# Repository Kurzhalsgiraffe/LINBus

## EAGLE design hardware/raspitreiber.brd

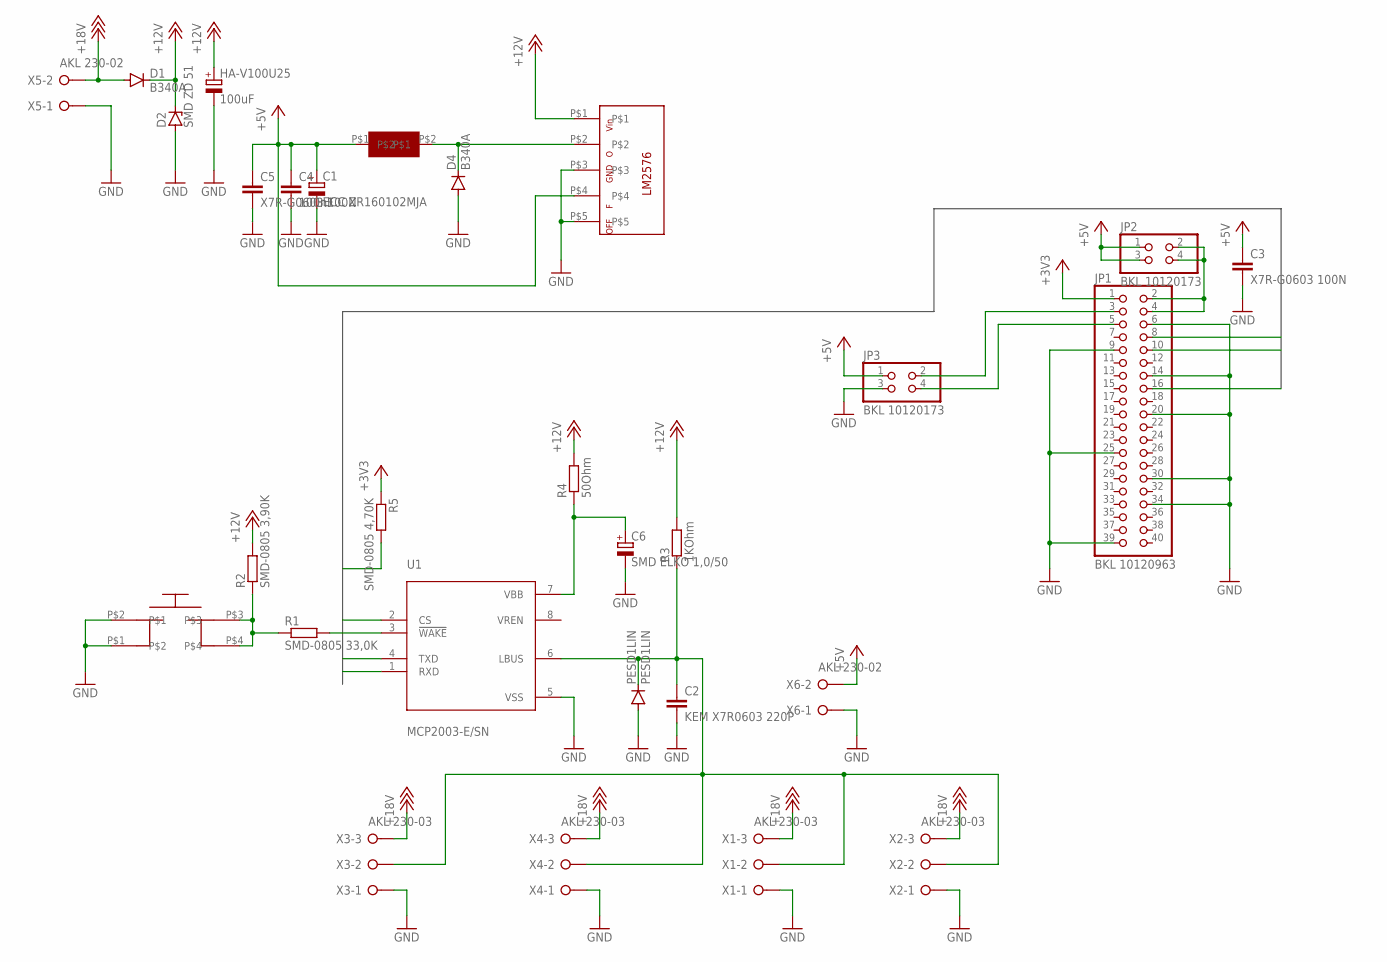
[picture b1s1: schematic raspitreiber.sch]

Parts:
C1: ECC ZR160102MJA; 153CLV-1012
C2: KEM X7R0603 220P; C0603
C3, C5: X7R-G0603 100N; C0603
C4: 100nF; C0603
C6: SMD ELKO 1,0/50; 150CLZ-0810
D1, D4: B340A; SMC
D2: SMD ZD 51; SOT23
HA-V100U25: 100uF; 153CLV-0807
JP1: BKL 10120963; 2X20
JP2, JP3: BKL 10120173; 2X02
L-09HVP100: LDEVICE7MM; LFOOT7MM
PESD1LIN: PESD1LIN; SOD323-W
R1: SMD-0805 33,0K; M0805
R2: SMD-0805 3,90K; M0805
R3: 1KOhm; M0805
R4: 50Ohm; M0805
R5: SMD-0805 4,70K; M0805
TASTER9313: SCHALTDEV; SCHALTFOOT
U1: MCP2003-E/SN; SOIC127P600X175-8N
U$1: LM2576
X1, X2, X3, X4: AKL 230-03; W237-3E
X5, X6: AKL 230-02; W237-132

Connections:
+3V3: JP1.1, R5.1
+5V: C1.+, C3.1, C4.1, C5.1, JP2.1, JP2.3, JP3.1, L-09HVP100.P$1, U$1.P$4, X6.2
+12V: D1.C, D2.3 (C), HA-V100U25.+, R2.2, R3.2, R4.2, U$1.P$1
+18V: D1.A, X1.3, X2.3, X3.3, X4.3, X5.2
CS: JP1.16, U1.2 (CS)
GND: C1.-, C2.2, C3.2, C4.2, C5.2, C6.-, D2.1 (A), D4.A, HA-V100U25.-, JP1.6, JP1.9, JP1.14, JP1.20, JP1.25, JP1.30, JP1.34, JP1.39, JP3.3, PESD1LIN.A, TASTER9313.P$1, TASTER9313.P$2, U1.5 (VSS), U$1.P$3, U$1.P$5, X1.1, X2.1, X3.1, X4.1, X5.1, X6.1
unnamed: D4.C, L-09HVP100.P$2, U$1.P$2
unnamed: C6.+, R4.1, U1.7 (VBB)
unnamed: R1.1, R2.1, TASTER9313.P$3, TASTER9313.P$4
unnamed: R1.2, U1.3 (!WAKE)
unnamed: C2.1, PESD1LIN.C, R3.1, U1.6 (LBUS), X1.2, X2.2, X3.2, X4.2
unnamed: JP1.2, JP1.4, JP2.2, JP2.4
unnamed: JP1.3, JP3.2
unnamed: JP1.5, JP3.4
RX: JP1.10, R5.2, U1.1 (RXD)
TX: JP1.8, U1.4 (TXD)

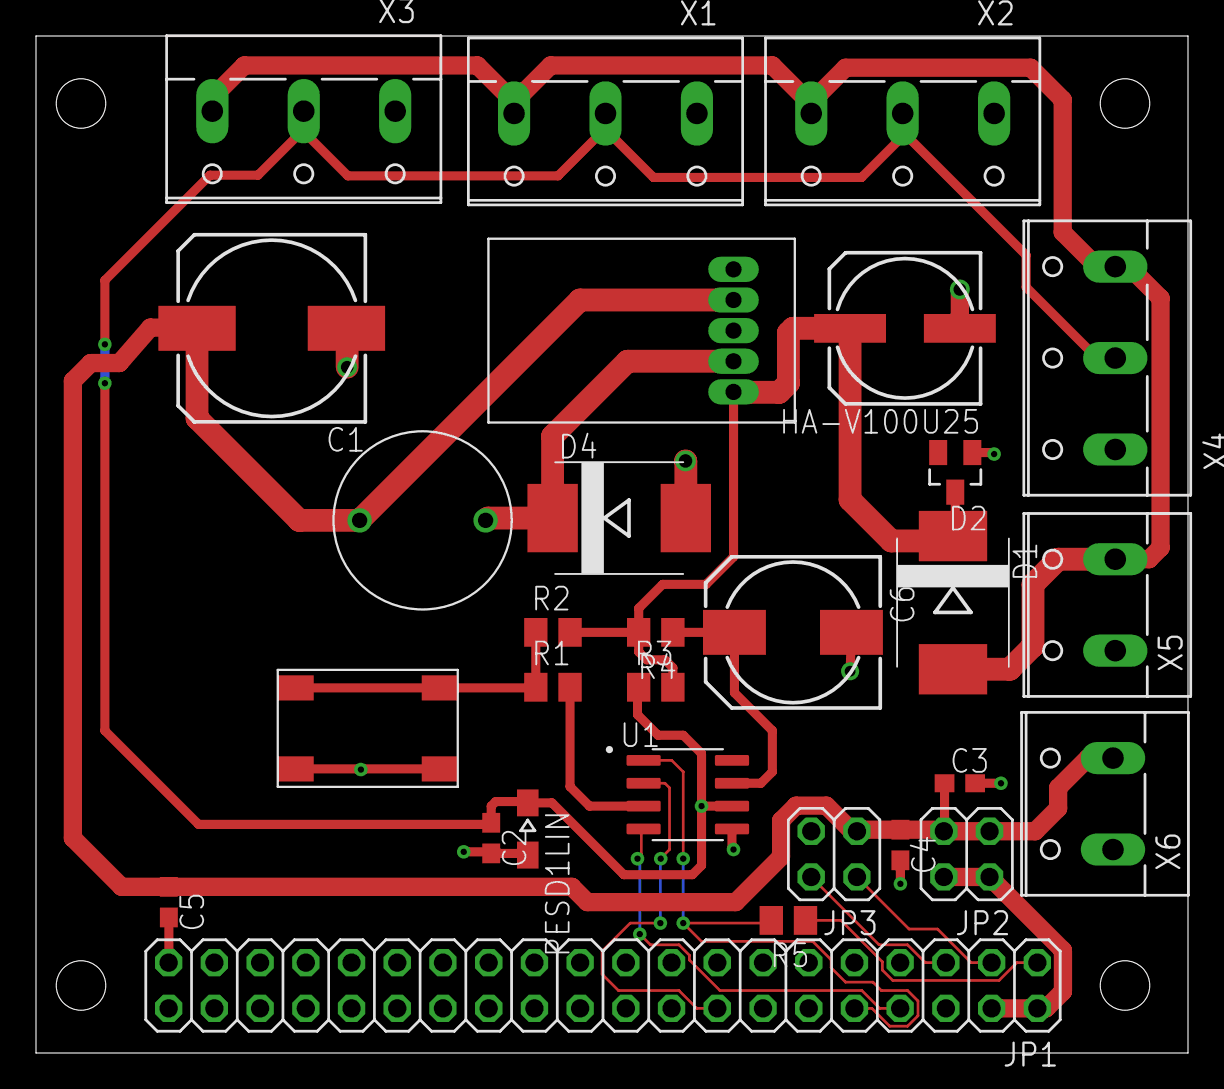
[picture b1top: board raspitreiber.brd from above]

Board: 2 copper layers, 64.0 x 56.5 mm, 29 parts (0 on the bottom side), 16 nets.

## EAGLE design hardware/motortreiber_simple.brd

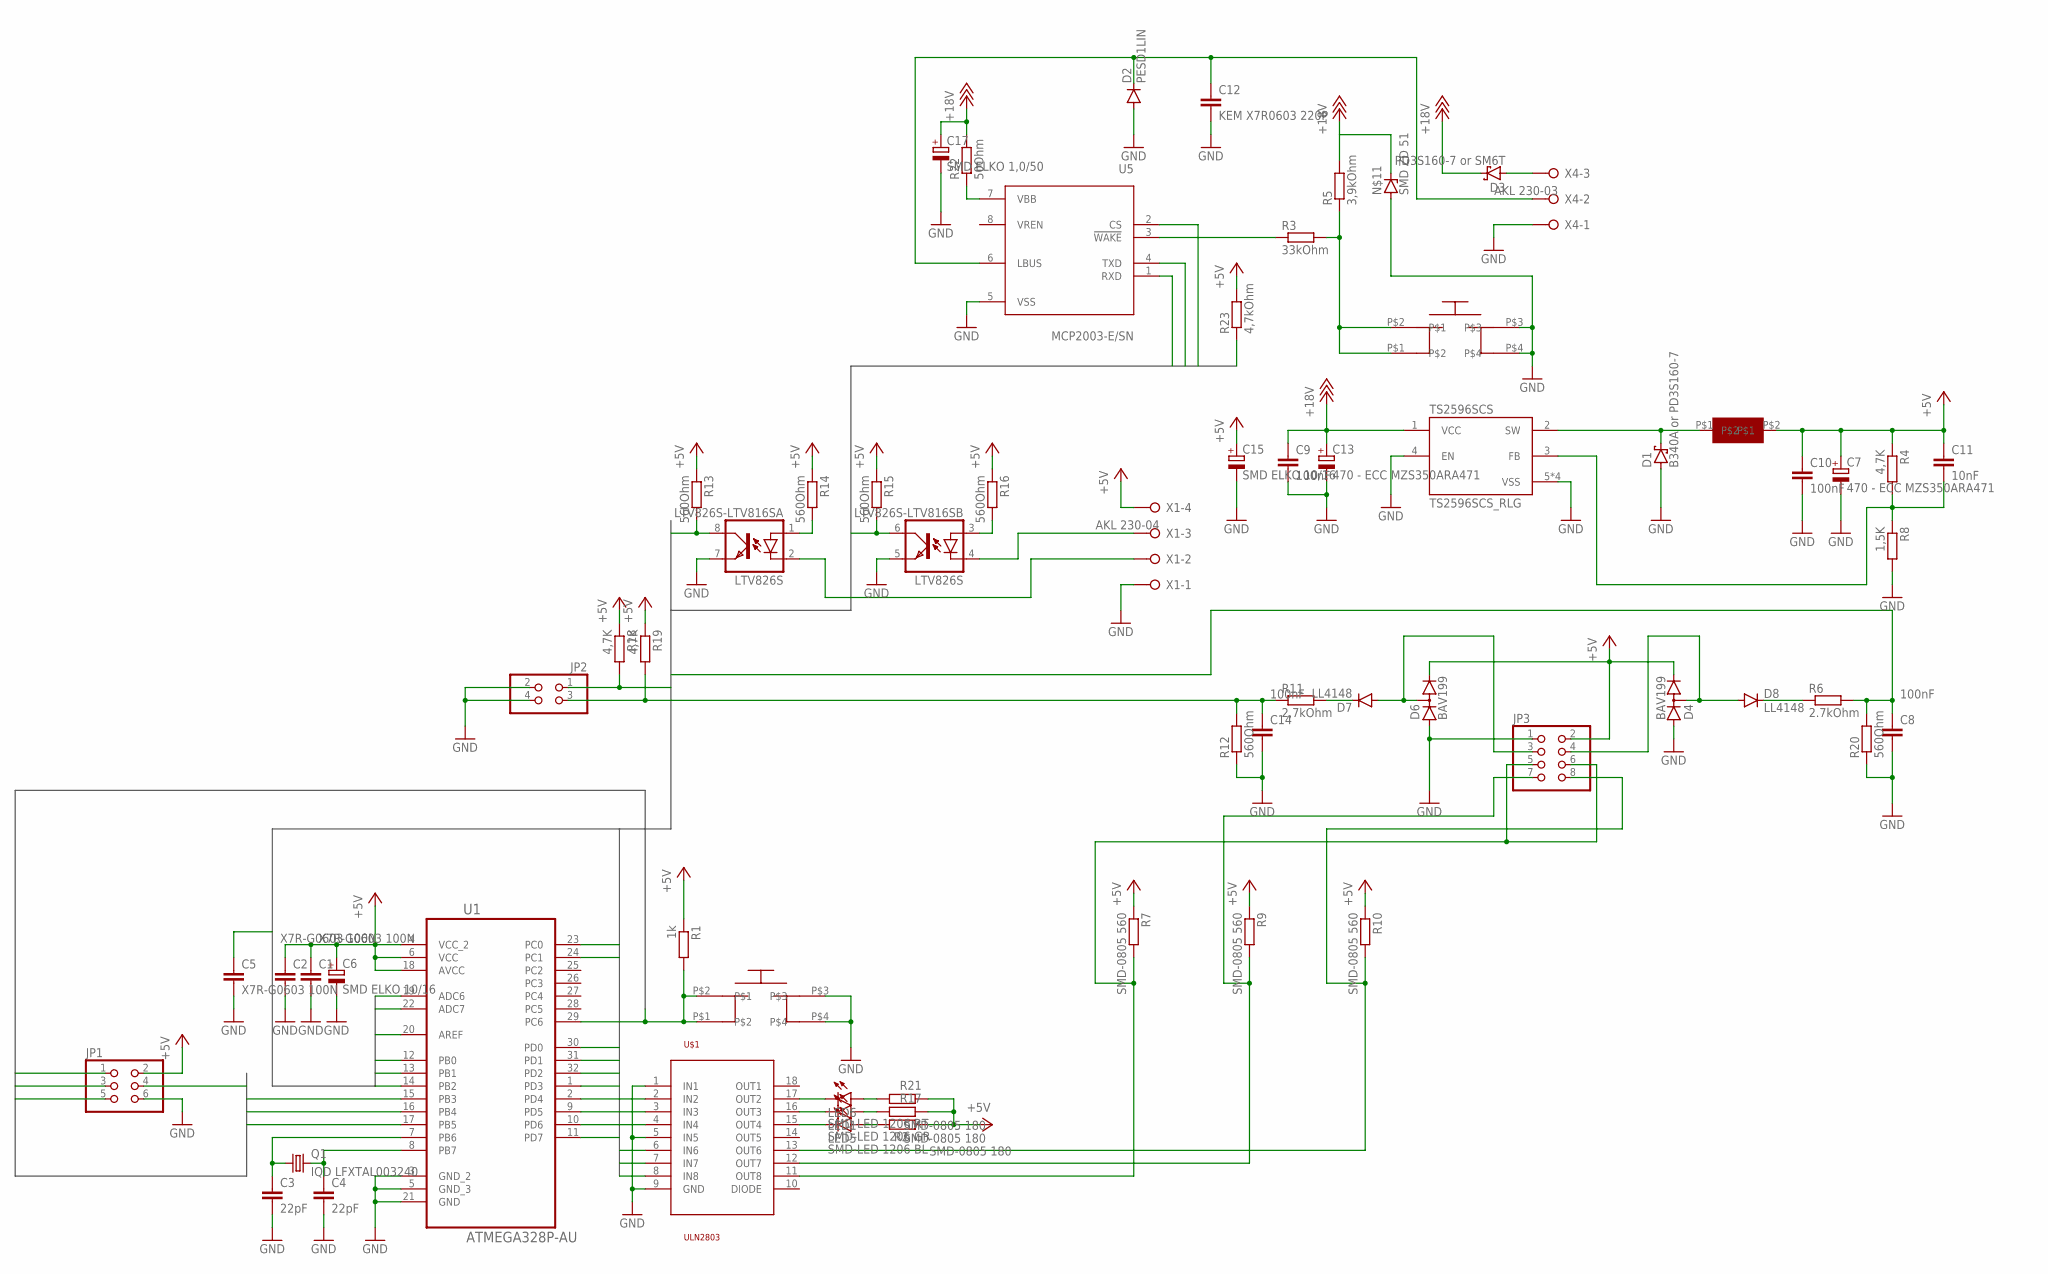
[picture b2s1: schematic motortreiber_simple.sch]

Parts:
C1, C2, C5: X7R-G0603 100N; C0603
C3, C4: 22pF; C0603
C6, C15: SMD ELKO 10/16; 153CLV-0505
C7, C13: 470 - ECC MZS350ARA471; 175TMP-0810
C8, C9, C10, C14: 100nF; C0603
C11: 10nF; C0603
C12: KEM X7R0603 220P; C0603
C17: SMD ELKO 1,0/50; 153CLV-0405
D1: B340A or PD3S160-7; SMB
D2: PESD1LIN; SOD323-W
D3: PD3S160-7 or SM6T; SMB
D4, D6: BAV199; SOT23
D7, D8: LL4148; SOD323-W
JP1: PINHD-2X3; 2X03
JP2: PINHD-2X2; 2X02
JP3: PINHD-2X4; 2X04
L-05HCP33: LDEVICE2-5MM; LFOOT2-5MM
LED1: SMD-LED 1206 GR; CHIPLED_1206
LED5: SMD-LED 1206 BL; CHIPLED_1206
LED6: SMD-LED 1206 RT; CHIPLED_1206
LTV826S-LTV816S: LTV826S; DIL8-SMD
N$11: SMD ZD 51; SOT23
Q1: IQD LFXTAL003240; HC49U-V
R1: 1k; R0805
R2, R17, R21: SMD-0805 180; R0805
R3: 33kOhm; R0805
R4, R18, R19: 4,7K; R0805
R5: 3,9kOhm; R0805
R6: 2.7kOhm; R0805
R7, R9, R10: SMD-0805 560; R0805
R8: 1,5K; R0805
R11: 2,7kOhm; R0805
R12, R13, R14, R15, R16, R20: 560Ohm; R0805
R22: 50Ohm; R0805
R23: 4,7kOhm; R0805
TASTER9313-1, TASTER9313-2: SCHALTDEV; SCHALTFOOT
TS2596SCS: TS2596SCS_RLG; SOP127P600X200-8N
U1: ATMEGA328P-AU; QFP80P900X900X120-32N
U5: MCP2003-E/SN; SOIC127P600X175-8N
U$1: ULN2803; SO18L
X1: AKL 230-04; W237-4P
X4: AKL 230-03; W237-3E

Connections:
+5V: C1.1, C2.1, C6.+, C7.+, C10.1, C11.1, C15.+, D4.2 (C), D6.2 (C), JP1.2, JP3.2, L-05HCP33.P$2, R1.1, R2.1, R4.1, R7.1, R9.1, R10.1, R13.1, R14.1, R15.1, R16.1, R17.1, R18.1, R19.1, R21.1, R23.2, U1.4 (VCC_2), U1.6 (VCC), U1.18 (AVCC), X1.4
+18V: C9.1, C13.+, C17.+, D3.C, N$11.3 (C), R5.2, R22.2, TS2596SCS.1 (VCC)
ADC6: C8.1, R6.2, R20.2, U1.19 (ADC6)
ADC7: C14.1, R11.1, R12.2, U1.22 (ADC7)
AREF: C5.1, U1.20 (AREF)
CLK: JP1.3, U1.17 (PB5)
GND: C1.2, C2.2, C3.2, C4.2, C5.2, C6.-, C7.-, C8.2, C9.2, C10.2, C12.2, C13.-, C14.2, C15.-, C17.-, D1.A, D2.A, D4.1 (A), D6.1 (A), JP1.6, JP2.2, JP2.4, JP3.1, LTV826S-LTV816S.5 (EMIT), LTV826S-LTV816S.7 (EMIT), N$11.1 (A), R8.2, R12.1, R20.1, TASTER9313-1.P$3, TASTER9313-1.P$4, TASTER9313-2.P$3, TASTER9313-2.P$4, TS2596SCS.4 (EN), TS2596SCS.5 (VSS), TS2596SCS.6 (VSS), TS2596SCS.7 (VSS), TS2596SCS.8 (VSS), U1.3 (GND_2), U1.5 (GND_3), U1.21 (GND), U5.5 (VSS), U$1.1 (IN1), U$1.5 (IN5), U$1.9 (GND), X1.1, X4.1
INT0: LTV826S-LTV816S.8 (COL), R13.2, U1.32 (PD2)
INT1: LTV826S-LTV816S.6 (COL), R15.2, U1.1 (PD3)
LED0: U1.12 (PB0), U$1.4 (IN4)
LED1: U1.13 (PB1), U$1.3 (IN3)
LED2: U1.14 (PB2), U$1.2 (IN2)
MISO: JP1.1, U1.16 (PB4)
MOSI: JP1.4, U1.15 (PB3)
unnamed: LTV826S-LTV816S.3 (A), R16.2
unnamed: LTV826S-LTV816S.4 (C), X1.3
unnamed: LTV826S-LTV816S.2 (C), X1.2
unnamed: LTV826S-LTV816S.1 (A), R14.2
unnamed: R22.1, U5.7 (VBB)
unnamed: LED6.C, U$1.17 (OUT2)
unnamed: LED5.A, R2.2
unnamed: LED1.A, R17.2
unnamed: C3.1, Q1.1, U1.7 (PB6)
unnamed: C4.1, Q1.2, U1.8 (PB7)
unnamed: C12.1, D2.C, U5.6 (LBUS), X4.2
unnamed: R3.1, U5.3 (!WAKE)
unnamed: D1.C, L-05HCP33.P$1, TS2596SCS.2 (SW)
unnamed: C11.2, R4.2, R8.1, TS2596SCS.3 (FB)
unnamed: JP3.5, JP3.6, R7.2, U$1.11 (OUT8)
unnamed: D6.3 (AC), D7.A, JP3.3
unnamed: R3.2, R5.1, TASTER9313-1.P$1, TASTER9313-1.P$2
unnamed: D3.A, X4.3
unnamed: D4.3 (AC), D8.A, JP3.4
unnamed: D7.C, R11.2
unnamed: JP3.7, R9.2, U$1.12 (OUT7)
unnamed: D8.C, R6.1
unnamed: LED1.C, U$1.16 (OUT3)
unnamed: LED6.A, R21.2
unnamed: LED5.C, U$1.15 (OUT4)
unnamed: JP3.8, R10.2, U$1.13 (OUT6)
NSLP: U1.2 (PD4), U5.2 (CS)
O0: U1.10 (PD6), U$1.7 (IN7)
O1: U1.11 (PD7), U$1.6 (IN6)
P0: JP2.3, R19.2, U1.23 (PC0)
P1: JP2.1, R18.2, U1.24 (PC1)
PWM: U1.9 (PD5), U$1.8 (IN8)
RESET: JP1.5, R1.2, TASTER9313-2.P$1, TASTER9313-2.P$2, U1.29 (PC6)
RX: R23.1, U1.30 (PD0), U5.1 (RXD)
TX: U1.31 (PD1), U5.4 (TXD)

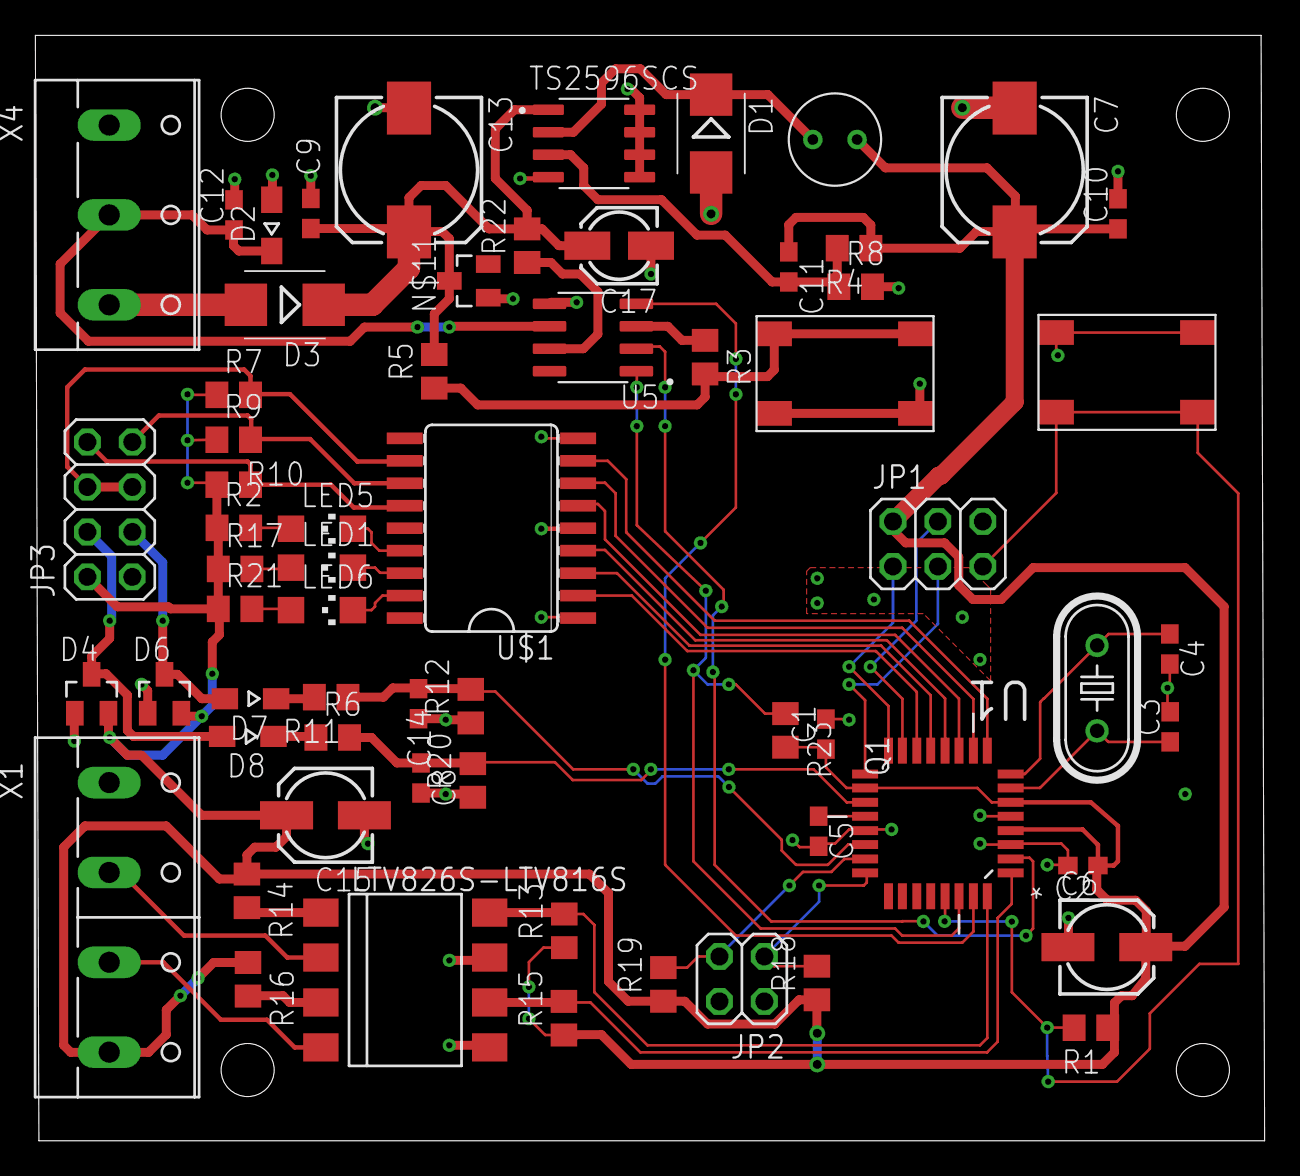
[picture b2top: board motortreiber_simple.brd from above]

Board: 2 copper layers, 69.5 x 62.5 mm, 64 parts (0 on the bottom side), 49 nets.

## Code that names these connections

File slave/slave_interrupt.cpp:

// #define F_CPU 16000000UL // CPU-Frequenz des ATmega328P (16 MHz)
#include <avr/io.h>
#include <avr/interrupt.h>
#include <unistd.h>
#include <signal.h>
#include <stdio.h>
#include <util/delay.h>

// LED Pins
#define BLUE_LED_PIN PB0
#define GREEN_LED_PIN PB1
#define RED_LED_PIN PB2

// Head Pins
#define HEAD_0_PIN PC0
#define HEAD_1_PIN PC1

// Read Transmit Pins
#define RX_PIN PD0
#define TX_PIN PD1
#define CS_PIN PD4

const uint16_t BAUD = 19200;

const unsigned int buffsize = 50;
uint8_t capture[buffsize];
uint8_t values[buffsize];

volatile uint8_t state = 0x0;
volatile uint16_t timer_overflow_counter = 0;
volatile uint8_t timer_value = 0;

uint8_t readBitD(uint8_t);

ISR(PCINT2_vect) {
  state = readBitD(RX_PIN);
  TCCR0B = 0; // Stop timer
  timer_value = TCNT0; // Get current timer value
  TCNT0 = 0; // Reset timer value
  timer_overflow_counter = 0; // Reset overflow counter
  TCCR0B = (1 << CS02) | (1 << CS00); // Set the timer prescaler to 1024; Timer ticks at 16,000,000 / 1024 = 15,625 Hz
}

ISR(TIMER0_OVF_vect) {
  timer_overflow_counter += 1; // When the 8-Bit Timer (TCNT0) overflows, this ISR is triggered
}

int slave_init() {
  cli();

  // LED Init
  DDRB |= (1 << BLUE_LED_PIN);  // OUT
  DDRB |= (1 << GREEN_LED_PIN); // OUT
  DDRB |= (1 << RED_LED_PIN);   // OUT

  // COM Pin Init
  DDRD &= ~(1 << RX_PIN); // IN
  DDRD |= (1 << TX_PIN);  // OUT
  DDRD |= (1 << CS_PIN);  // OUT

  PORTD |= (1 << CS_PIN); // HIGH

  DDRC |= (1 << HEAD_0_PIN); // OUT
  DDRC |= (1 << HEAD_1_PIN); // OUT

  PORTC &= ~(1 << HEAD_0_PIN); // LOW
  PORTC &= ~(1 << HEAD_1_PIN); // LOW

  // https://www.arxterra.com/11-atmega328p-external-interrupts/
  // https://stackoverflow.com/questions/70049553/best-way-to-handle-multiple-pcint-in-avr
  PCICR |= (1 << PCIE2);    // group 2
  PCMSK2 |= (1 << PCINT16); // set PCINT16 to interrupt

  // Timer Registers
  // https://www.mikrocontroller.net/articles/AVR-GCC-Tutorial/Die_Timer_und_Z%C3%A4hler_des_AVR
  TCCR0A = 0;
  TCCR0B = (1 << CS02) | (1 << CS00); // Set the timer prescaler to 1024; Timer ticks at 16,000,000 / 1024 = 15,625 Hz
  TIMSK0 |= (1 << TOIE0);             // overflow erlauben

  sei();
  return 0;
}

void writeBitD(uint8_t pin, uint8_t value) {
  if (value) {
    PORTD |= (1 << pin); // Write 1
  } else {
    PORTD &= ~(1 << pin); // Write 0
  }
}

void writeBitC(uint8_t pin, uint8_t value) {
  if (value) {
    PORTC |= (1 << pin); // Write 1
  } else {
    PORTC &= ~(1 << pin); // Write 0
  }
}

uint8_t readBitD(uint8_t pin) {
  return (PIND & (1 << pin)) ? 0x1 : 0x0;
}

uint8_t calculate_checksum(uint8_t data_low, uint8_t data_high) {
  uint16_t checksum = 0;
  checksum += data_low;
  checksum += data_high;
  return checksum & 0xFF;
}

void led(uint8_t pin, uint8_t value) {
  if (value) {
    PORTB |= (1 << pin); // LED einschalten
  } else {
    PORTB &= ~(1 << pin); // LED ausschalten
  }
}

void pulse(uint8_t width) {
  if (width == 1) {
    writeBitC(HEAD_0_PIN, 1);
    writeBitC(HEAD_1_PIN, 1);
    _delay_us((1000000 * 5) / (2 * BAUD));
    writeBitC(HEAD_0_PIN, 0);
    writeBitC(HEAD_1_PIN, 0);
    _delay_us((1000000 * 5) / (2 * BAUD));
  }
  else {
    writeBitC(HEAD_0_PIN, 1);
    writeBitC(HEAD_1_PIN, 1);
    _delay_us((1000000 * 5) / (BAUD));
    writeBitC(HEAD_0_PIN, 0);
    writeBitC(HEAD_1_PIN, 0);
    _delay_us((1000000 * 5) / (BAUD));
  }
}

void sendbyte(uint8_t byte) {
  for (uint8_t i = 0; i < 8; i++) {
    writeBitC(HEAD_0_PIN, 0);
    writeBitC(HEAD_1_PIN, 0);
    _delay_us((1000000 * 5) / (2 * BAUD));
  }

  writeBitC(HEAD_0_PIN, 1);
  writeBitC(HEAD_1_PIN, 1);
  _delay_us((1000000 * 5) / (2 * BAUD));

  for (uint8_t i = 0; i < 8; i++) {

    if (((byte >> i) & 0x01) == 0x01) {
      writeBitC(HEAD_0_PIN, 1);
      writeBitC(HEAD_1_PIN, 1);
      _delay_us((1000000 * 5) / (2 * BAUD));
    }
    else {
      writeBitC(HEAD_0_PIN, 0);
      writeBitC(HEAD_1_PIN, 0);
      _delay_us((1000000 * 5) / (2 * BAUD));
    }
  }

  writeBitC(HEAD_0_PIN, 1);
  writeBitC(HEAD_1_PIN, 1);
  _delay_us((1000000 * 5) / (2 * BAUD));
  writeBitC(HEAD_0_PIN, 1);
  writeBitC(HEAD_1_PIN, 1);
  _delay_us((1000000 * 5) / (2 * BAUD));
}

uint8_t convertTicksToBitNum(uint8_t num) {
  const uint8_t thresholds[] = {
      4, 12, 20, 28, 38, 45, 55, 64, 72, 80, 88, 95, 105, 115};

  for (uint8_t i = 0; i < sizeof(thresholds); i++) {
    if (num <= thresholds[i]) {
      return i;
    }
  }
  return 0x0;
}

uint8_t convertTicksToBitNum2(uint8_t ticks) {
  uint8_t num = (ticks * 10000) / 8474;
  if (num % 10 > 5) {
    return (num / 10) + 1;
  }
  return (num / 10);
}

uint8_t getsyncbytefromheader(uint8_t current_index) {
  uint32_t temp = 0;
  uint8_t pos = 0;
  for (uint8_t i = 2; i < current_index; i++) {
    uint8_t num = convertTicksToBitNum(capture[i]);
    for (uint8_t j = 0; j < num; j++) {
      if (values[i] == 1) {
        temp |= 0x00000001 << pos;
      }
      pos++;
    }
  }
  temp &= 0x03FC00;
  return (uint8_t)(temp >> 10);
}

uint8_t getpidbytefromheader(uint8_t current_index) {
  uint32_t temp = 0;
  uint8_t pos = 0;
  for (uint8_t i = 2; i < current_index; i++) {
    uint8_t num = convertTicksToBitNum(capture[i]);
    for (uint8_t j = 0; j < num; j++) {
      if (values[i] == 1) {
        temp |= 0x00000001 << pos;
      }
      pos++;
    }
  }
  temp &= 0x01FE;
  return (uint8_t)(temp >> 1);
}

int main() {
  slave_init();

  uint8_t currentstate = 0;
  uint8_t current_index = 0;

  for (uint8_t i = 0; i < buffsize; i++) { // Initialising arrays with Zeros
    capture[i] = 0x0;
    values[i] = 0x0;
  }

  while (1) {
    if (current_index >= buffsize) { // Buffer Overflow, infinite red LED blinking to indicate error
      while (1) {
        led(RED_LED_PIN, 1);
        _delay_us(100000);
        led(RED_LED_PIN, 0);
        _delay_us(100000);
      }
    }

    if (currentstate == 0 && state == 0x1) { // Rising Edge (High -> Low)
      currentstate = 1;

      if (timer_value > 100) {
        current_index = 0;
      }

      capture[current_index] = timer_value;
      values[current_index] = 1;
      current_index++;
    }

    if (currentstate == 1 && state == 0x0) { // Falling Edge (Low -> High)
      currentstate = 0;
      // pulse(2);

      if (timer_value > 100) {
        current_index = 0;
      }
      capture[current_index] = timer_value;
      values[current_index] = 0;
      current_index++;
    }

    if (currentstate == 1 && state == 0x1) { // State unchanged High
      if (timer_overflow_counter == 1) { // If timer has overflowed once (256 ticks, i.e. 255*64us = 16.384ms). This timespan goes from 16.384ms to 32.704ms after last timer reset
        sendbyte(getsyncbytefromheader(current_index));
      }
    }
  }

#ifdef BLUBBER
  uint16_t result = 0xFFFF;
  while (1) {
    while (1) {
      uint8_t bit = readBitD(RX_PIN);
      if (bit == 0) {
        break;
      }
    }
    while (1) {
      uint8_t bit = readBitD(RX_PIN);
      if (bit == 1) {
        break;
      }
    }
    while (1) {
      uint8_t bit = readBitD(RX_PIN);
      result <<= 1;
      result |= (bit & 0x01);

      writeBitC(HEAD_0_PIN, 1);
      writeBitC(HEAD_1_PIN, 1);
      _delay_us((1000000 * 10.045) / (2 * BAUD));
      writeBitC(HEAD_0_PIN, 0);
      writeBitC(HEAD_1_PIN, 0);
      _delay_us((1000000 * 10.045) / (2 * BAUD));

      if ((result & 0x3FFF) == 0x0001) {

        break;
      }
    }
    result = 0xFFFF;
    while (1) {
      uint8_t bit = readBitD(RX_PIN);
      result <<= 1;
      result |= (bit & 0x01);

      writeBitC(HEAD_0_PIN, 1);
      writeBitC(HEAD_1_PIN, 1);
      _delay_us((1000000 * 10.045) / (2 * BAUD));
      writeBitC(HEAD_0_PIN, 0);
      writeBitC(HEAD_1_PIN, 0);
      _delay_us((1000000 * 10.045) / (2 * BAUD));

      if ((result & 0x007F) == 0x0055) {
        /*led(RED_LED_PIN, 1);
          _delay_us(100000);
          led(RED_LED_PIN, 0);
          _delay_us(100000);*/
        break;
      }
    }
  }
#endif
  return 0;
}

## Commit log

2024-11-19 init
2024-11-19 successfully send messageId
2024-11-19 Daten senden und empfangen
2024-11-19 check for checksum and message_id
2024-11-26 ADD: Stand 2024_11_26 ADD: Netlist
2024-11-28 organized
2024-11-28 improved code quality
2024-11-29 interrupt experiment
    (von rembold)
2024-11-30 test
2024-11-30 got rid of division by float
2024-12-01 fixed compiling issues; also cleaned code
2024-12-01 cycle_buffer
2024-12-03 241203
